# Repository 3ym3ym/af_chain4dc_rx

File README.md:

# af_chain4dc_rx
AF chain for DC receiver

This little project was created to complete the standalone direct conversion (DC) receiver. Other parts of the receiver are:
 - Main board (input filter, quadrature mixer, AF preamps, phasing SSB demodulator). Si5351A board from Adafruit (or Aliexpress clone) is attached to it.
 - Control board. Can be any microcontroller running the qudrature VFO code. I am currently using RP2040 SuperMini, 0.96" SSD1306 OLED display and 360PPI optical encoder.

The idea behind the whole project is to build a high performance SSB/CW receiver using only cheap parts readily available from Aliexpress or other similar sources.

Included files are the KiCAD 9.0 project (schematic and PCB) which uses SMD footprints. It can be modified to use through hole footprints. All parts are available in TH variants.

The first stage is a simple CE amplifier, also used to set the bias point to the following filter stages. The gain (and the input impedance) is set by R15.

I picked the idea of the low-pass audio filter from Asshar Farhan, VU2ESE. The actual filter design was done using the online Filter Wizard tool from Analog Devices, then tweaked while simulating in LTSpice. The values listed in the schematic result in -3dB point about 2.0kHz. At 5kHz the attenuation is -50dB. I used 5% resistors and 10% capacitors. The frequency response is not as sharp as the simulated with the ideal values, but is good enough and I like the sound of SSB coming through the filter. I am not a CW guy, modifying the filter for CW is left as an exercise for the reader.

The final amplifier is a standard TDA2822 circuit, with a jumper to change the gain. It has significantly lower hiss than LM386 and the Chinese fakes seem to work well.

The circuit works down to 3V. I am using a cheap ME6209 3.3V LDO, which requires a good output bypass capacitor, otherwise there is a bit of ringing at the maximum volume (because of the feedback from the PA back to the input stage through the power rail). 100uF aluminum plus 10uF ceramic capacitors is not an overkill.

ME6209 claims to tolerate up to 18V input, which I haven't tested. The dropout is small enough to use a single LiIon cell as the input power source, or 12V if that is what you have in the receiver.

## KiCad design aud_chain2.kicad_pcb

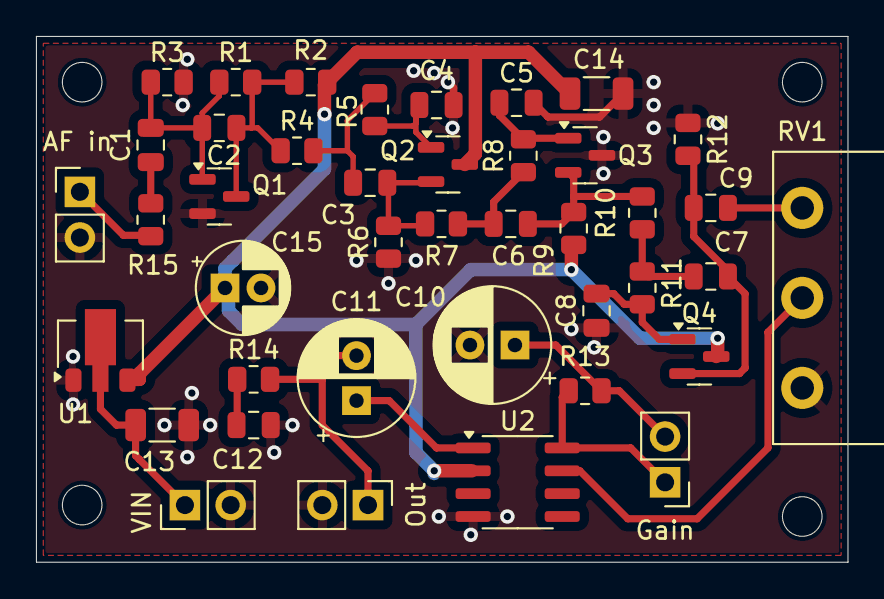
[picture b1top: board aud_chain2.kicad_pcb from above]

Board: 2 copper layers, 45.1 x 29.2 mm, 41 parts (0 on the bottom side), 23 nets.

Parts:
C1, C9: 1u; C_0805_2012Metric
C2, C4: 1n; C_0805_2012Metric
C3, C6, C7: 22n; C_0805_2012Metric
C5: 10n; C_0805_2012Metric
C8: 15n; C_0805_2012Metric
C10: 100x6.3v; CP_Radial_D6.3mm_P2.50mm
C11: 100x6.3V; CP_Radial_D6.3mm_P2.50mm
C12: 100n; C_0805_2012Metric
C13, C14: 10u; C_1206_3216Metric
C15: 47x6.3v; CP_Radial_D5.0mm_P2.00mm
J1: AF in; PinHeader_1x02_P2.54mm_Vertical
J2: Gain; PinHeader_1x02_P2.54mm_Vertical
J3: Out; PinHeader_1x02_P2.54mm_Vertical
J4: VIN; PinHeader_1x02_P2.54mm_Vertical
Q1, Q2, Q4: MMBT3904; SOT-23
Q3: MMBT3906; SOT-23
R1, R3: 47k; R_0805_2012Metric
R2, R6, R9, R12: 1k; R_0805_2012Metric
R4, R15: 10k; R_0805_2012Metric
R5: 27k; R_0805_2012Metric
R7: 3k9; R_0805_2012Metric
R8, R11: 5k6; R_0805_2012Metric
R10: 2k4; R_0805_2012Metric
R13: 680; R_0805_2012Metric
R14: 4.7; R_0805_2012Metric
RV1: 10k; Potentiometer_Piher_PC-16_Single_Horizontal
U1: ME6209; SOT-89-3
U2: TDA2822D; SOIC-8_3.9x4.9mm_P1.27mm

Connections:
3V3: C14.1, C15.1, Q2.3 (C), Q4.3 (C), R2.1, R9.2, U1.3 (VOUT), U2.2
GND: C4.1, C5.1, C8.1, C10.2, C12.1, C13.2, C14.2, C15.2, J1.2, J3.2, J4.2, Q1.2 (E), Q3.3 (C), R3.2, R6.1, R12.1, RV1.1, U1.1 (GND), U2.4
unnamed: C1.1, R15.2
unnamed: C3.1, R4.2, R5.1
unnamed: C6.1, R7.2, R8.1
unnamed: C7.1, R10.2, R11.1
unnamed: C9.2, RV1.3
unnamed: C11.1, U2.1
unnamed: C12.2, R14.1
unnamed: J1.1, R15.1
unnamed: J2.1, R13.2, U2.8
unnamed: C10.1, J2.2, R13.1
unnamed: C11.2, J3.1, R14.2
unnamed: C13.1, J4.1, U1.2 (VIN)
unnamed: C1.2, C2.2, Q1.1 (B), R1.1, R3.1
unnamed: C2.1, Q1.3 (C), R1.2, R2.2, R4.1
unnamed: C4.2, Q2.1 (B), R5.2
unnamed: C3.2, Q2.2 (E), R6.2, R7.1
unnamed: C5.2, Q3.1 (B), R8.2
unnamed: C6.2, Q3.2 (E), R9.1, R10.1
unnamed: C8.2, Q4.1 (B), R11.2
unnamed: C7.2, C9.1, Q4.2 (E), R12.2
unnamed: RV1.2, U2.7
